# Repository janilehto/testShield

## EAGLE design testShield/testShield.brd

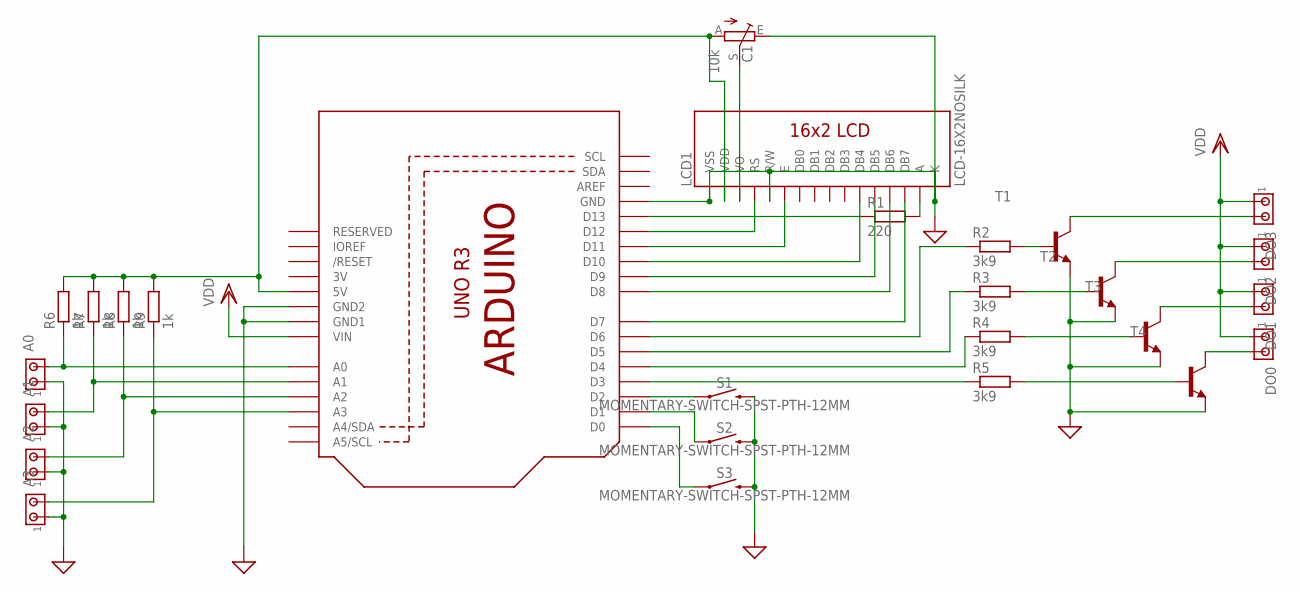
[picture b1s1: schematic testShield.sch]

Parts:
A0, A1, A2, A3: MTA02-156; 1X2MTA
C1: 10k; CA9V
DO0, DO1, DO2, DO3: MTA02-156; 1X2MTA
LCD1: LCD-16X2NOSILK; LCD-16X2_NOSILK
R1: 220; 0617/22
R2, R3, R4, R5: 3k9; 0207/12
R6, R7, R8, R9: 1k; 0207/12
S1, S2, S3: MOMENTARY-SWITCH-SPST-PTH-12MM; TACTILE_SWITCH_PTH_12MM
T1, T2, T3, T4: BC547-NPN-TO92-CBE; TO92-CBE
U1: ARDUINOR3-BPLACE

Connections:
3V: U1.3V
GND: A0.1, A1.1, A2.1, A3.1, C1.E, LCD1.1 (VSS), LCD1.5 (R/W), LCD1.16 (K), S1.3 (2), S2.3 (2), S3.3 (2), T1.E, T2.E, T3.E, T4.E, U1.GND, U1.GND1, U1.GND2
unnamed: R2.2, T1.B
unnamed: LCD1.15 (A), R1.2
unnamed: R1.1, U1.D13
unnamed: S1.1, U1.D2
unnamed: C1.S, LCD1.3 (VO)
unnamed: LCD1.4 (RS), U1.D12
unnamed: LCD1.6 (E), U1.D11
unnamed: LCD1.11 (DB4), U1.D10
unnamed: LCD1.12 (DB5), U1.D9
unnamed: LCD1.13 (DB6), U1.D8
unnamed: LCD1.14 (DB7), U1.D7
unnamed: S2.1, U1.D1
unnamed: S3.1, U1.D0
unnamed: R2.1, U1.D6
unnamed: R3.1, U1.D5
unnamed: R4.1, U1.D4
unnamed: R5.1, U1.D3
unnamed: R5.2, T4.B
unnamed: R4.2, T3.B
unnamed: R3.2, T2.B
unnamed: DO3.2, T1.C
unnamed: DO2.2, T2.C
unnamed: DO1.2, T3.C
unnamed: DO0.2, T4.C
unnamed: A0.2, R6.1, U1.A0
unnamed: A1.2, R7.1, U1.A1
unnamed: A2.2, R8.1, U1.A2
unnamed: A3.2, R9.1, U1.A3
unnamed: C1.A, LCD1.2 (VDD), R6.2, R7.2, R8.2, R9.2, U1.5V
VDD: DO0.1, DO1.1, DO2.1, DO3.1, U1.VIN

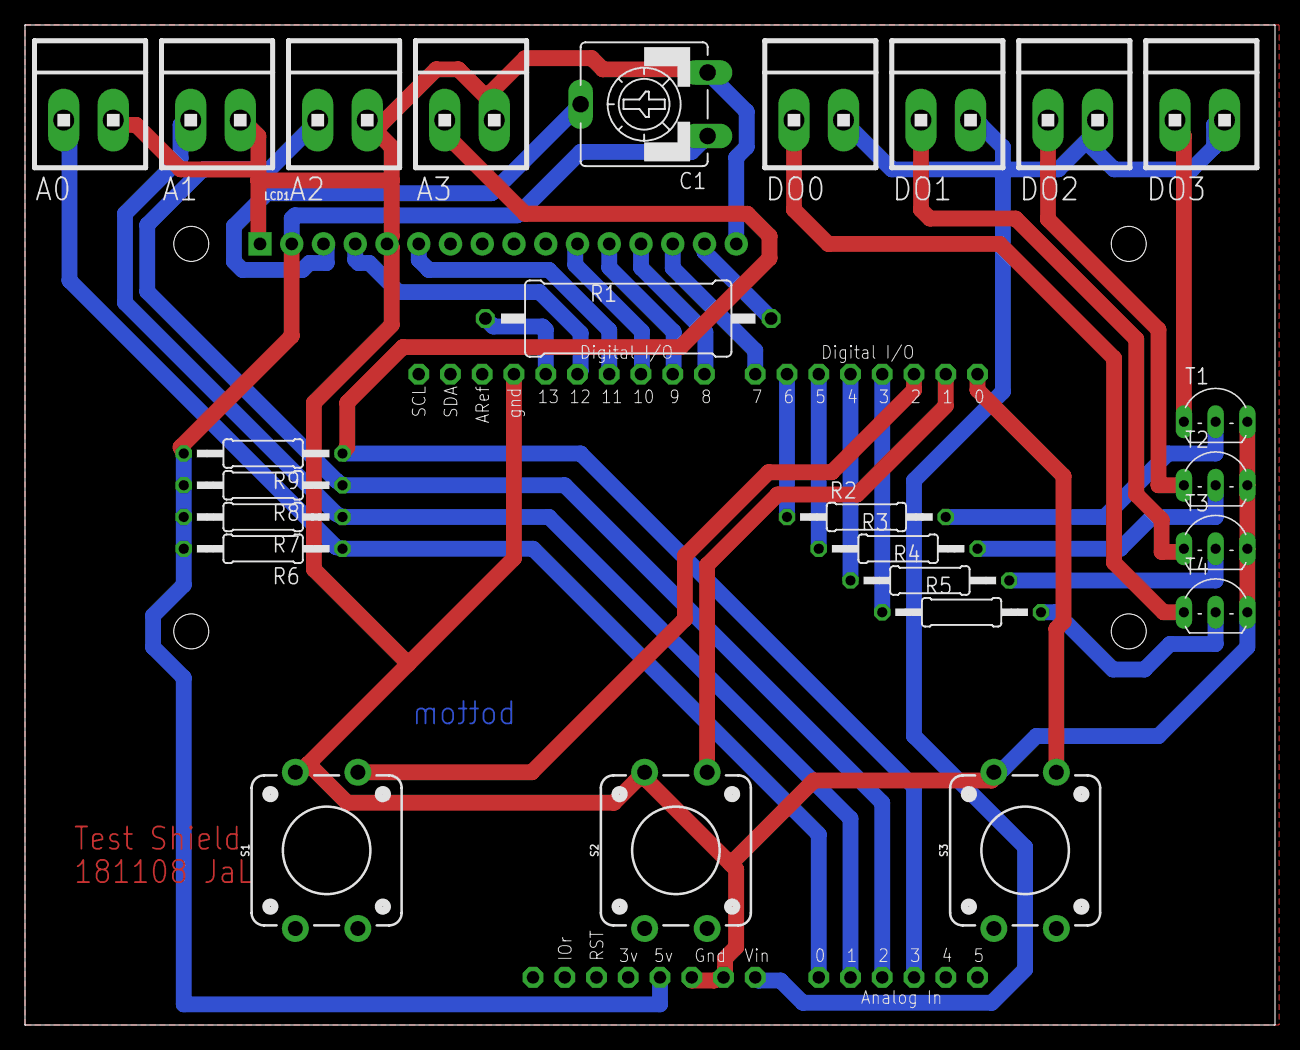
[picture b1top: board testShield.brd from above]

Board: 2 copper layers, 100.0 x 80.0 mm, 27 parts (0 on the bottom side), 31 nets.

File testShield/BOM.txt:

Partlist exported from //fs1/homeFolders$/jani.lehto/Documents/Arduino/testShield/testShield/testShield.sch at 12.11.2018 9.15

Part Value                          Device                         Package                 Description                                                                                                                 PROD_ID    SF_ID     SF_SKU    SPICEPREFIX
A0                                  MTA02-156                      1X2MTA                  AMP connector                                                                                                                                                         
A1                                  MTA02-156                      1X2MTA                  AMP connector                                                                                                                                                         
A2                                  MTA02-156                      1X2MTA                  AMP connector                                                                                                                                                         
A3                                  MTA02-156                      1X2MTA                  AMP connector                                                                                                                                                         
C1   10k                            TRIM_EU-CA9V                   CA9V                    POTENTIOMETER                                                                                                                                                         
DO0                                 MTA02-156                      1X2MTA                  AMP connector                                                                                                                                                         
DO1                                 MTA02-156                      1X2MTA                  AMP connector                                                                                                                                                         
DO2                                 MTA02-156                      1X2MTA                  AMP connector                                                                                                                                                         
DO3                                 MTA02-156                      1X2MTA                  AMP connector                                                                                                                                                         
LCD1 LCD-16X2NOSILK                 LCD-16X2NOSILK                 LCD-16X2_NOSILK         Standard text-only 16x2 parallel input LCD                                                                                             LCD-00255                      
R1   220                            R-EU_0617/22                   0617/22                 RESISTOR, European symbol                                                                                                                                  R          
R2   3k9                            R-EU_0207/12                   0207/12                 RESISTOR, European symbol                                                                                                                                  R          
R3   3k9                            R-EU_0207/12                   0207/12                 RESISTOR, European symbol                                                                                                                                  R          
R4   3k9                            R-EU_0207/12                   0207/12                 RESISTOR, European symbol                                                                                                                                  R          
R5   3k9                            R-EU_0207/12                   0207/12                 RESISTOR, European symbol                                                                                                                                  R          
R6   1k                             R-EU_0207/12                   0207/12                 RESISTOR, European symbol                                                                                                                                  R          
R7   1k                             R-EU_0207/12                   0207/12                 RESISTOR, European symbol                                                                                                                                  R          
R8   1k                             R-EU_0207/12                   0207/12                 RESISTOR, European symbol                                                                                                                                  R          
R9   1k                             R-EU_0207/12                   0207/12                 RESISTOR, European symbol                                                                                                                                  R          
S1   MOMENTARY-SWITCH-SPST-PTH-12MM MOMENTARY-SWITCH-SPST-PTH-12MM TACTILE_SWITCH_PTH_12MM Momentary Switch (Pushbutton) - SPST                                                                                        SWCH-09185           COM-09190            
S2   MOMENTARY-SWITCH-SPST-PTH-12MM MOMENTARY-SWITCH-SPST-PTH-12MM TACTILE_SWITCH_PTH_12MM Momentary Switch (Pushbutton) - SPST                                                                                        SWCH-09185           COM-09190            
S3   MOMENTARY-SWITCH-SPST-PTH-12MM MOMENTARY-SWITCH-SPST-PTH-12MM TACTILE_SWITCH_PTH_12MM Momentary Switch (Pushbutton) - SPST                                                                                        SWCH-09185           COM-09190            
T1                                  BC547-NPN-TO92-CBE             TO92-CBE                NPN Transistror                                                                                                                                                       
T2                                  BC547-NPN-TO92-CBE             TO92-CBE                NPN Transistror                                                                                                                                                       
T3                                  BC547-NPN-TO92-CBE             TO92-CBE                NPN Transistror                                                                                                                                                       
T4                                  BC547-NPN-TO92-CBE             TO92-CBE                NPN Transistror                                                                                                                                                       
U1   ARDUINOR3-BPLACE               ARDUINOR3-BPLACE               ARDUINOR3-BPLACE        This is a new object for the new Arduino R3 - with extra pins that you may want to use (such as IOref, and duplicated A4/A5

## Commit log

2018-11-12 Included files
2018-11-14 Added Button.lib/started menu
2018-11-14 Added Button.lib/started menubuilding
2018-11-15 Up/down buttons working
2018-11-15 Added comments, updated TODO
2018-11-15 drawCursor() adjust

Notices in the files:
parts and their libraries:
SparkFun-Displays: Licensing: Creative Commons ShareAlike 4.0 International - https://creativecommons.org/licenses/by-sa/4.0
